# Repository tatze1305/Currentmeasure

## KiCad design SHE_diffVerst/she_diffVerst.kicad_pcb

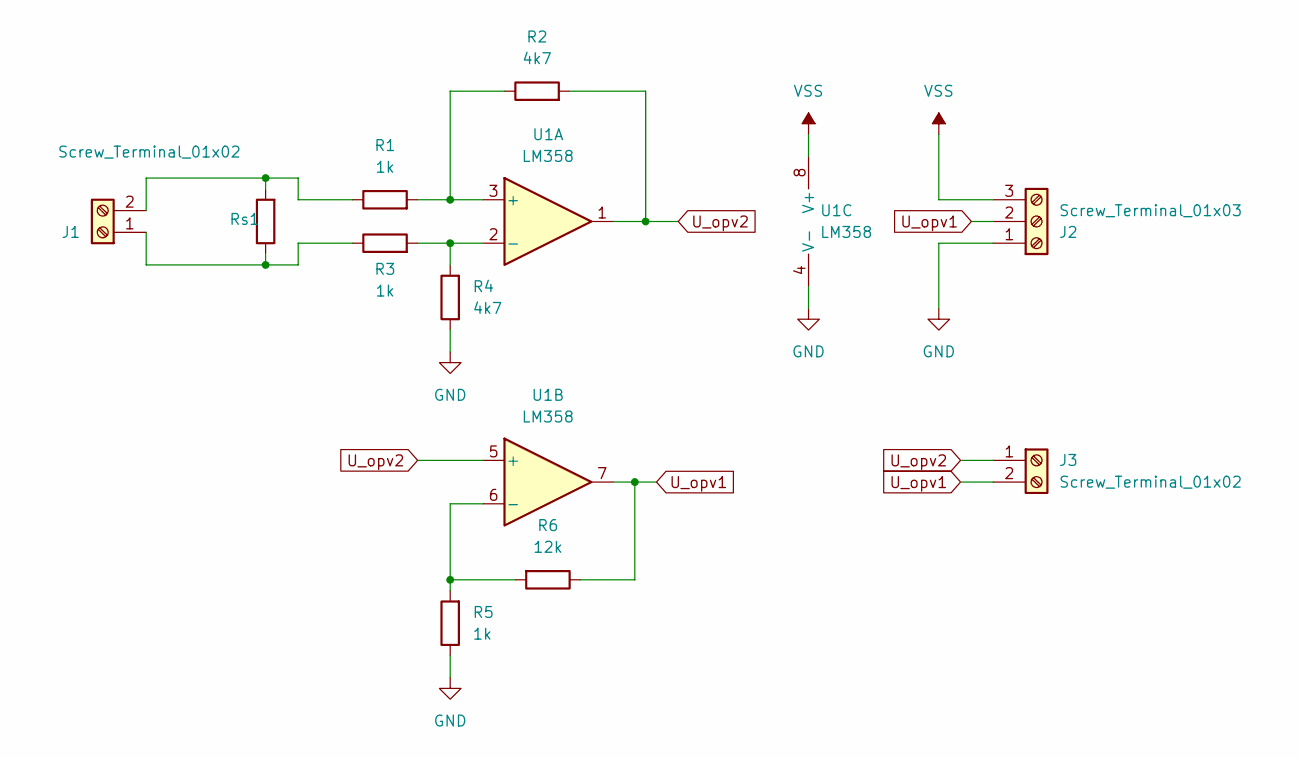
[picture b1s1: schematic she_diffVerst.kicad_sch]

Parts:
J1: Screw_Terminal_01x02; TerminalBlock_RND_205-00001_1x02_P5.00mm_Horizontal
J2: Screw_Terminal_01x03; TerminalBlock_RND_205-00013_1x03_P5.00mm_Horizontal
J3: Screw_Terminal_01x02; PhoenixContact_MSTBA_2,5_2-G-5,08_1x02_P5.08mm_Horizontal
R1, R3, R5: 1k; R_Axial_DIN0207_L6.3mm_D2.5mm_P10.16mm_Horizontal
R2, R4: 4k7; R_Axial_DIN0207_L6.3mm_D2.5mm_P10.16mm_Horizontal
R6: 12k; R_Axial_DIN0207_L6.3mm_D2.5mm_P10.16mm_Horizontal
Rs1: R_shunt; R_2512_6332Metric_Pad1.40x3.35mm_HandSolder
U1: LM358; DIP-8_W7.62mm_Socket

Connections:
GND: J2.1, R4.1, R5.1, U1.4 (V-)
unnamed: J1.1, R3.1, Rs1.1
unnamed: J1.2, R1.1, Rs1.2
unnamed: R1.2, R2.1, U1.3 (+)
unnamed: R3.2, R4.2, U1.2 (-)
unnamed: R5.2, R6.2, U1.6 (-)
U_opv1: J2.2, J3.2, R6.1, U1.7
U_opv2: J3.1, R2.2, U1.1, U1.5 (+)
VSS: J2.3, U1.8 (V+)

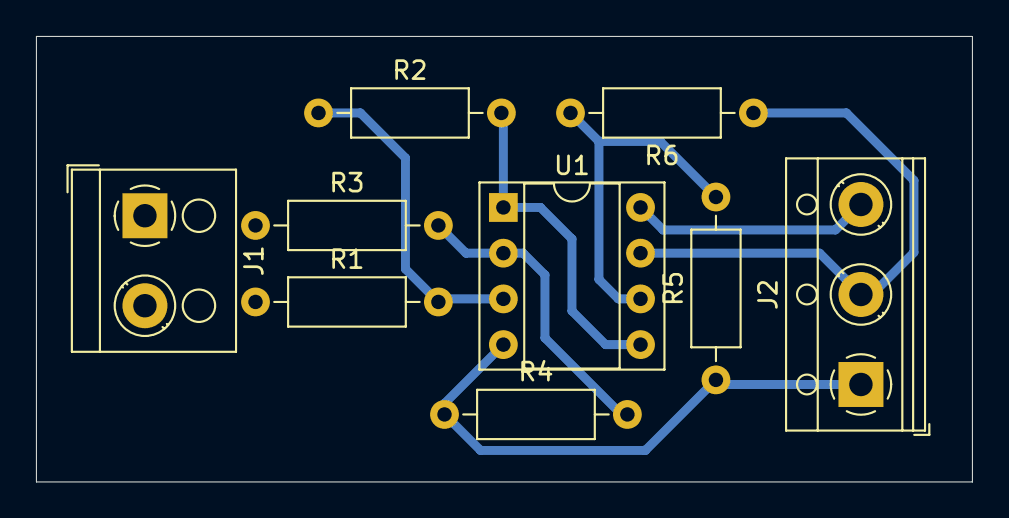
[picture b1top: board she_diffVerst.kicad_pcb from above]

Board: 2 copper layers, 52.0 x 24.8 mm, 10 parts (1 on the bottom side), 9 nets.

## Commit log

2024-12-10 init commi
